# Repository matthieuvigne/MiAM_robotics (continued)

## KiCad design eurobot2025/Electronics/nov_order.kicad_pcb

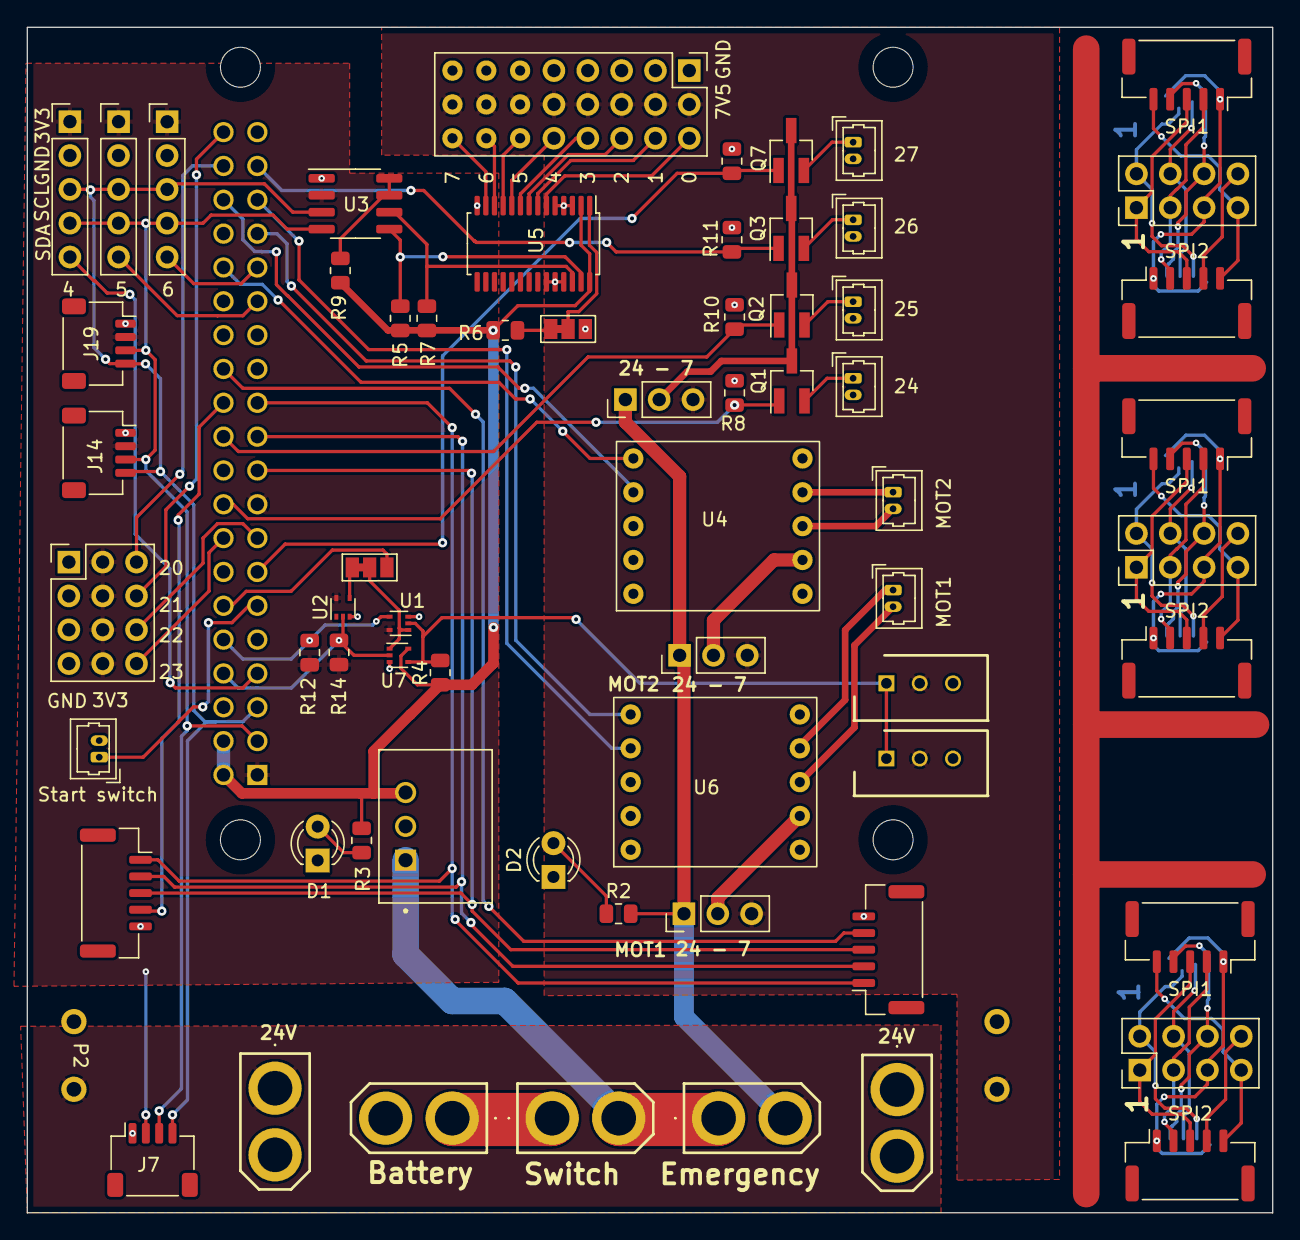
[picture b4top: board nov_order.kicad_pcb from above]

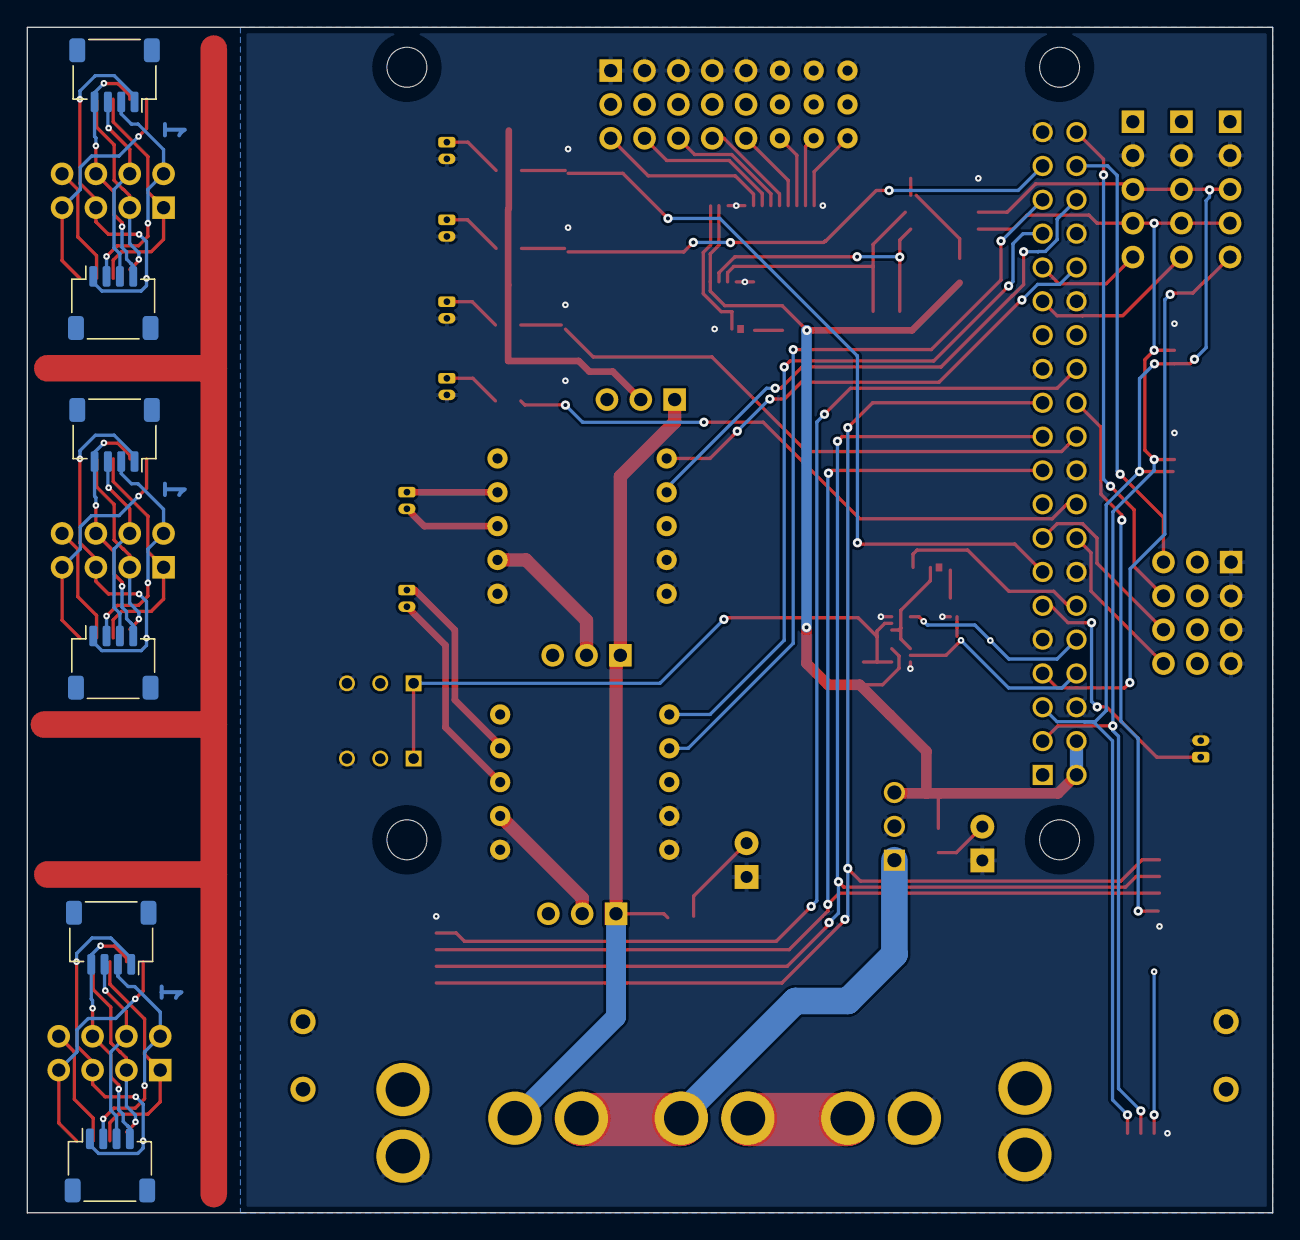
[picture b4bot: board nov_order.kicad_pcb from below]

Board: 2 copper layers, 93.5 x 89.0 mm, 73 parts (7 on the bottom side), 61 nets.

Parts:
C3: Conn_03x08; Pin_Header_Straight_3x08_Pitch2.54mm
C4: Conn_03x04; Pin_Header_Straight_3x04_Pitch2.54mm
D1, D2: LED; LED_D3.0mm
J1: PI40HAT; MODULE_RASPBERRY_PI_B+
J1#2, J1#3, J1#4, J3#2, J3#3, J3#4, J7, J14, J19: Conn_01x04_Male; JST_SH_SM04B-SRSS-TB_1x04-1MP_P1.00mm_Horizontal
J2, J2#2, J2#3: Conn_02x05_Odd_Even; PinHeader_2x04_P2.54mm_Vertical
J2#4, J3, J4, J5, J6: Conn_01x02_Male; XT30UM
J8, J10, J12, J13, J15, J16, J24: Conn_01x02_Male; Molex_PicoBlade_53047-0210_1x02_P1.25mm_Vertical
J9, J23: 22-03-5035; SHDR3W60P0X250_1X3_990X490X590P
J11, J17, J18: Conn_01x03_Male; PinHeader_1x03_P2.54mm_Vertical
J20, J21, J22: Conn_01x05; PinHeader_1x05_P2.54mm_Vertical
JP1, JP2: SolderJumper_3_Bridged12; SolderJumper-3_P1.3mm_Bridged12_Pad1.0x1.5mm_NumberLabels
P1: R-78Bxx-2.0; CONV_R-78Bxx-2.0
P2: Amazon 10A stepdown; StepDown10A
Q1, Q2, Q3, Q7: NVTR4503NT1G; SOT-23_Handsoldering
R1, R4, R6, R8, R10, R11, R12, R14: 10k; R_0805_2012Metric
R2, R3: R; R_0805_2012Metric
R5, R7: 5k; R_0805_2012Metric
R9: 200k; R_0805_2012Metric
SPI0, SPI1, SPI1#2, SPI1#3, SPI2, SPI2#2, SPI2#3, SPI2#4: JST_ZH5; JST_GH_SM05B-GHS-TB_1x05-1MP_P1.25mm_Horizontal
U1: 74LVC1G125; SOT-553
U2: SN74LVC1G04DRLR; SOT-553
U3: PCA9306D; SOP-8_3.76x4.96mm_P1.27mm
U4, U6: Pololu_MAX14870; PololuMAX14870
U5: PCA9685PW; TSSOP-28_4.4x9.7mm_P0.65mm
U7: SN74AHCT1G126; SOT-553

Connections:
+3.3V: C4.2, C4.5, C4.8, C4.11, J1.1 (P3V3), J1.17 (P3V3), J1#2.2, J1#3.2, J1#4.2, J2.2, J2#2.2, J2#3.2, J3#2.2, J3#3.2, J3#4.2, J7.2, J14.2, J19.2, J20.1, J21.1, J22.1, R12.2, R14.2, U1.5 (VCC), U2.5 (VCC), U3.2 (VREF1)
+5V: J1.2 (P5V), J1.4 (P5V), P1.3, R3.2, R4.2, R5.2, R6.2, R7.2, R9.2, U5.2 (A1), U5.28 (VDD), U7.5 (VCC)
+7.5V: C3.2, C3.5, C3.8, C3.11, C3.14, C3.17, C3.20, C3.23, J9.2, J11.3, J17.3, J18.3, J23.2, P2.3
+24V: J4.2, J5.1, J6.1, J11.1, J17.1, J18.1, P2.1, R2.2
/A0: JP2.2 (C), U5.1 (A0)
/GPIO 4: J1.7 (BCM4), J20.5
/GPIO 5: J1.29 (BCM5), J21.5
/GPIO 6: J1.31 (BCM6), J22.5
/GPIO 12: J1.32 (BCM12), U4.1 (PWM)
/GPIO 13: J1.33 (BCM13), U6.1 (PWM)
/GPIO 16: J1.36 (BCM16), U4.2 (DIR)
/GPIO 17: J1.11 (BCM17), J24.1
/GPIO 19: J1.35 (BCM19), U6.2 (DIR)
/GPIO 20: C4.3, J1.38 (BCM20)
/GPIO 21: C4.6, J1.40 (BCM21)
/GPIO 22: C4.9, J1.15 (BCM22)
/GPIO 23: C4.12, J1.16 (BCM23)
/GPIO 24: J1.18 (BCM24), Q1.1 (G), R8.2
/GPIO 25: J1.22 (BCM25), Q2.1 (G), R10.2
/GPIO 26: J1.37 (BCM26), Q3.1 (G), R11.2
/GPIO 27: J1.13 (BCM27), Q7.1 (G), R1.2
/I2C SCL: J1.5 (BCM3), J1#2.4, J1#3.4, J1#4.4, J2.6, J2#2.6, J2#3.6, J3#2.4, J3#3.4, J3#4.4, J7.4, J14.4, J19.4, J20.3, J21.3, J22.3, SPI1.4, SPI1#2.4, SPI1#3.4, U3.3 (SCL1)
/I2C SDA: J1.3 (BCM2), J1#2.3, J1#3.3, J1#4.3, J2.4, J2#2.4, J2#3.4, J3#2.3, J3#3.3, J3#4.3, J7.3, J14.3, J19.3, J20.4, J21.4, J22.4, U3.4 (SDA1)
/SPI MISO: J2.3, J2#2.3, J2#3.3, SPI1.2, SPI1#2.2, SPI1#3.2, SPI2#2.2, SPI2#3.2, SPI2#4.2
/SPI MOSI: J2.1, J2#2.1, J2#3.1, SPI1.3, SPI1#2.3, SPI1#3.3, SPI2#2.3, SPI2#3.3, SPI2#4.3
/SPI_CS1: J2.8, J2#2.8, J2#3.8, SPI2#2.4, SPI2#3.4, SPI2#4.4
/Servo DIR: J1.12 (BCM18), JP1.3 (B)
/TX_EN: JP1.2 (C), U1.1, U7.1
/UART_HalfDuplex: J9.1, J23.1, R4.1, U1.2, U7.4
/UART_RX: J1.10 (BCM15), R12.1, U1.4
/UART_TX: J1.8 (BCM14), R14.1, U2.2, U7.2
GND: C3.1, C3.4, C3.7, C3.10, C3.13, C3.16, C3.19, C3.22, C4.1, C4.4, C4.7, C4.10, D1.1 (K), D2.1 (K), J1.6 (GND), J1.9 (GND), J1.14 (GND), J1.20 (GND), J1.25 (GND), J1.30 (GND), J1.34 (GND), J1.39 (GND), J2.7, J2#2.7, J2#3.7, J3.2, J5.2, J6.2, J7.1, J9.3, J12.2, J13.2, J14.1, J15.2, J16.2, J19.1, J20.2, J21.2, J22.2, J23.3, J24.2, JP2.3 (B), P1.2, P2.2, R1.1, R8.1, R10.1, R11.1, SPI0.5, SPI1.5, SPI1#2.5, SPI1#3.5, SPI2.5, SPI2#2.5, SPI2#3.5, SPI2#4.5, U1.3 (GND), U2.3 (GND), U3.1 (GND), U4.4 (nEnable), U4.5 (GND), U5.3 (A2), U5.4 (A3), U5.5 (A4), U5.14 (VSS), U5.23 (~OE), U5.24 (A5), U5.25 (EXTCLK), U6.4 (nEnable), U6.5 (GND), U7.3 (GND)
GNDA: J1#2.1, J1#3.1, J1#4.1, J2.5, J2#2.5, J2#3.5, J3#2.1, J3#3.1, J3#4.1, SPI1.1, SPI1#2.1, SPI1#3.1, SPI2#2.1, SPI2#3.1, SPI2#4.1
unnamed: D1.2 (A), R3.1
unnamed: D2.2 (A), R2.1
unnamed: J2#4.1, J3.1
unnamed: J2#4.2, J4.1, P1.1
unnamed: J8.1, U6.7 (M1)
unnamed: J8.2, U6.8 (M2)
unnamed: J10.1, U4.7 (M1)
unnamed: J10.2, U4.8 (M2)
unnamed: J12.1, Q7.2 (S)
unnamed: J13.1, Q1.2 (S)
unnamed: J15.1, Q2.2 (S)
unnamed: J16.1, Q3.2 (S)
unnamed: J17.2, U6.9 (Vin)
unnamed: J18.2, U4.9 (Vin)
unnamed: JP1.1 (A), U2.4
unnamed: JP2.1 (A), R6.1
unnamed: R9.1, U3.7 (VREF2), U3.8 (EN)
unnamed: R7.1, U3.6 (SCL2), U5.26 (SCL)
unnamed: R5.1, U3.5 (SDA2), U5.27 (SDA)
unnamed: C3.3, U5.6 (LED0)
unnamed: C3.6, U5.7 (LED1)
unnamed: C3.9, U5.8 (LED2)
unnamed: C3.12, U5.9 (LED3)
unnamed: C3.15, U5.10 (LED4)
unnamed: C3.18, U5.11 (LED5)
unnamed: C3.21, U5.12 (LED6)
unnamed: C3.24, U5.13 (LED7)
VCCQ: J11.2, Q1.3 (D), Q2.3 (D), Q3.3 (D), Q7.3 (D)
